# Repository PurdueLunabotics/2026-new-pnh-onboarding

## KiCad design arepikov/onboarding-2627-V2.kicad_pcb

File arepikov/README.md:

This is not your folder! Please make your own.

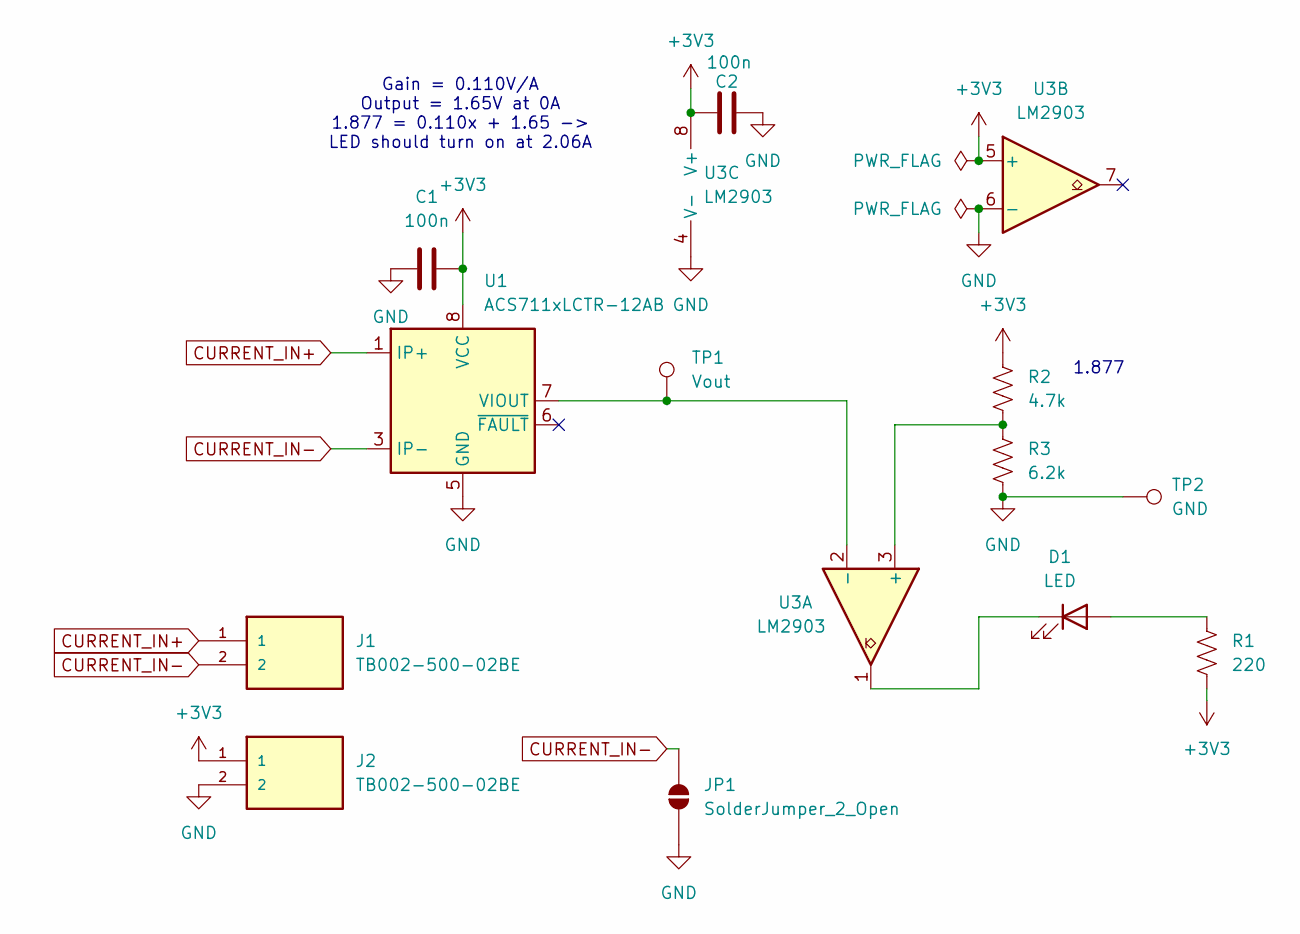
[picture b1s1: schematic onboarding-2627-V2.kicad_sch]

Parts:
C1, C2: 100n; C_0805_2012Metric
D1: LED; LED_D5.0mm
J1, J2: TB002-500-02BE; CUI_TB002-500-02BE
JP1: SolderJumper_2_Open; Wide_solderjumper
R1: 220; R_Axial_DIN0411_L9.9mm_D3.6mm_P12.70mm_Horizontal
R2: 4.7k; R_Axial_DIN0411_L9.9mm_D3.6mm_P12.70mm_Horizontal
R3: 6.2k; R_Axial_DIN0411_L9.9mm_D3.6mm_P12.70mm_Horizontal
TP1: Vout; TestPoint_Pad_D1.5mm
TP2: GND; TestPoint_Pad_D1.5mm
U1: ACS711xLCTR-12AB; SOIC-8_3.9x4.9mm_P1.27mm
U3: LM2903; DIP-8_W7.62mm

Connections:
+3V3: C1.2, C2.2, J2.1, R1.2, R2.1, U1.8 (VCC), U3.5 (+), U3.8 (V+)
CURRENT_IN+: J1.1, U1.1 (IP+), U1.2 (IP+)
CURRENT_IN-: J1.2, JP1.2 (B), U1.3 (IP-), U1.4 (IP-)
GND: C1.1, C2.1, J2.2, JP1.1 (A), R3.2, TP2.1 (1_1), U1.5 (GND), U3.4 (V-), U3.6 (-)
unnamed: D1.2 (A), R1.1
unnamed: D1.1 (K), U3.1
unnamed: TP1.1 (1_1), U1.7 (VIOUT), U3.2 (-)
unnamed: R2.2, R3.1, U3.3 (+)

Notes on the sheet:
Gain = 0.110V/A Output = 1.65V at 0A 1.877 = 0.110x + 1.65 -> LED should turn on at 2.06A
1.877

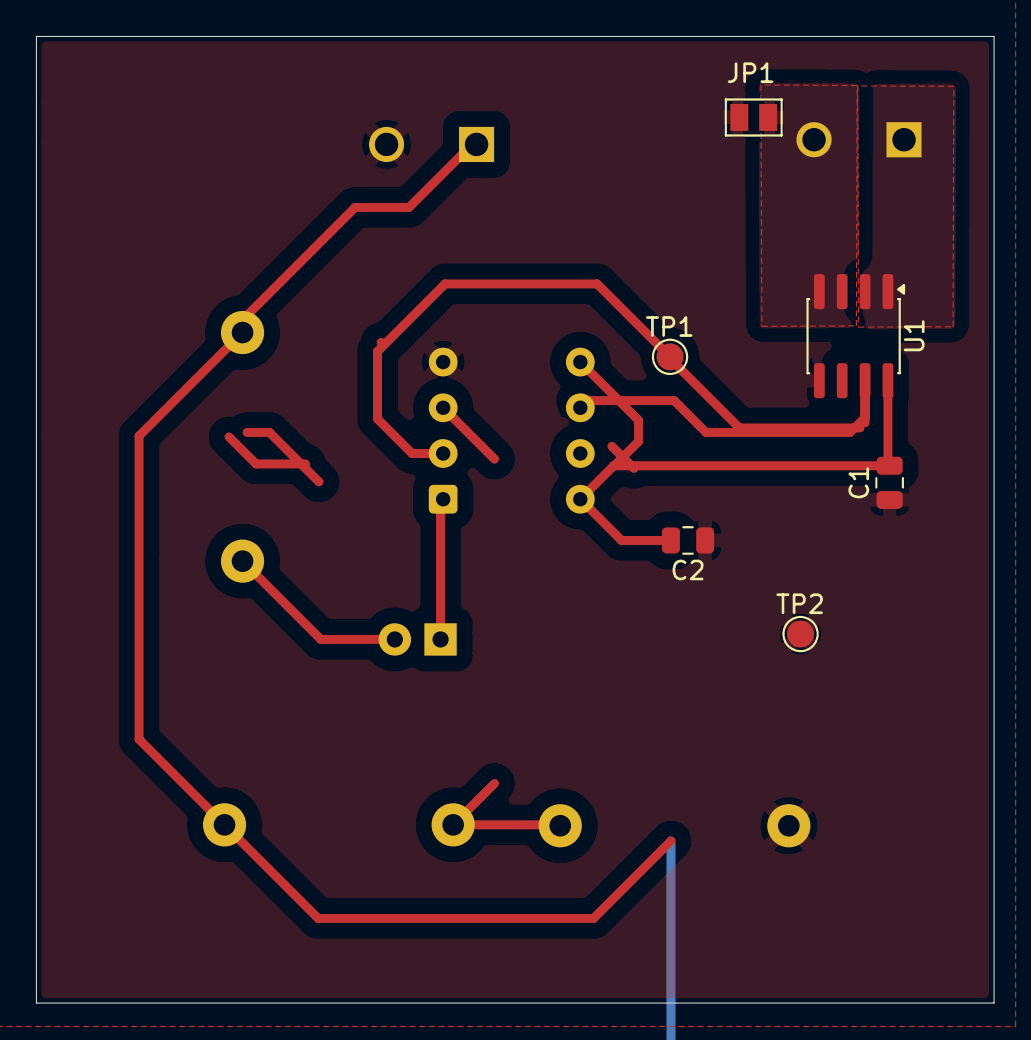
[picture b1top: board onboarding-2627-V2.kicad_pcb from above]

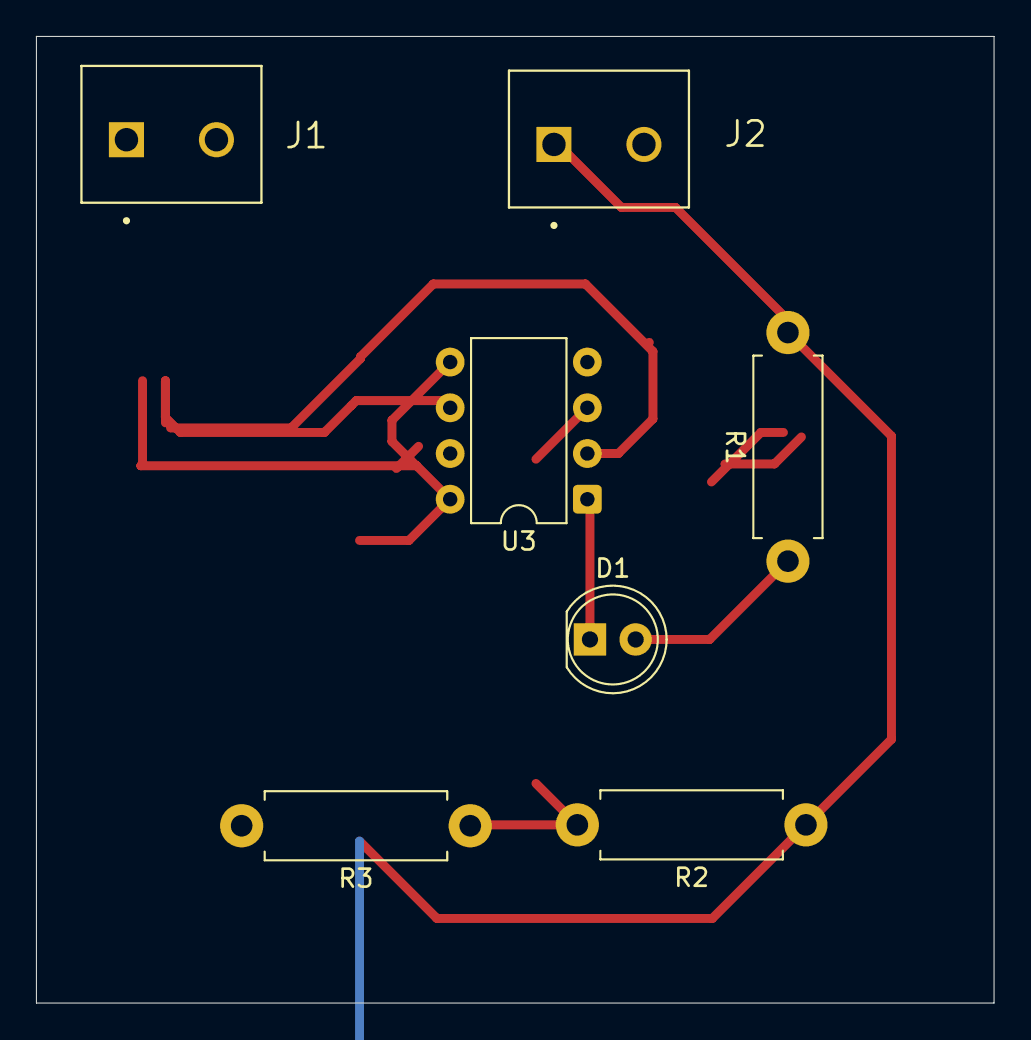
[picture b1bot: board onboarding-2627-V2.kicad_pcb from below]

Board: 2 copper layers, 53.2 x 53.7 mm, 13 parts (7 on the bottom side), 8 nets.

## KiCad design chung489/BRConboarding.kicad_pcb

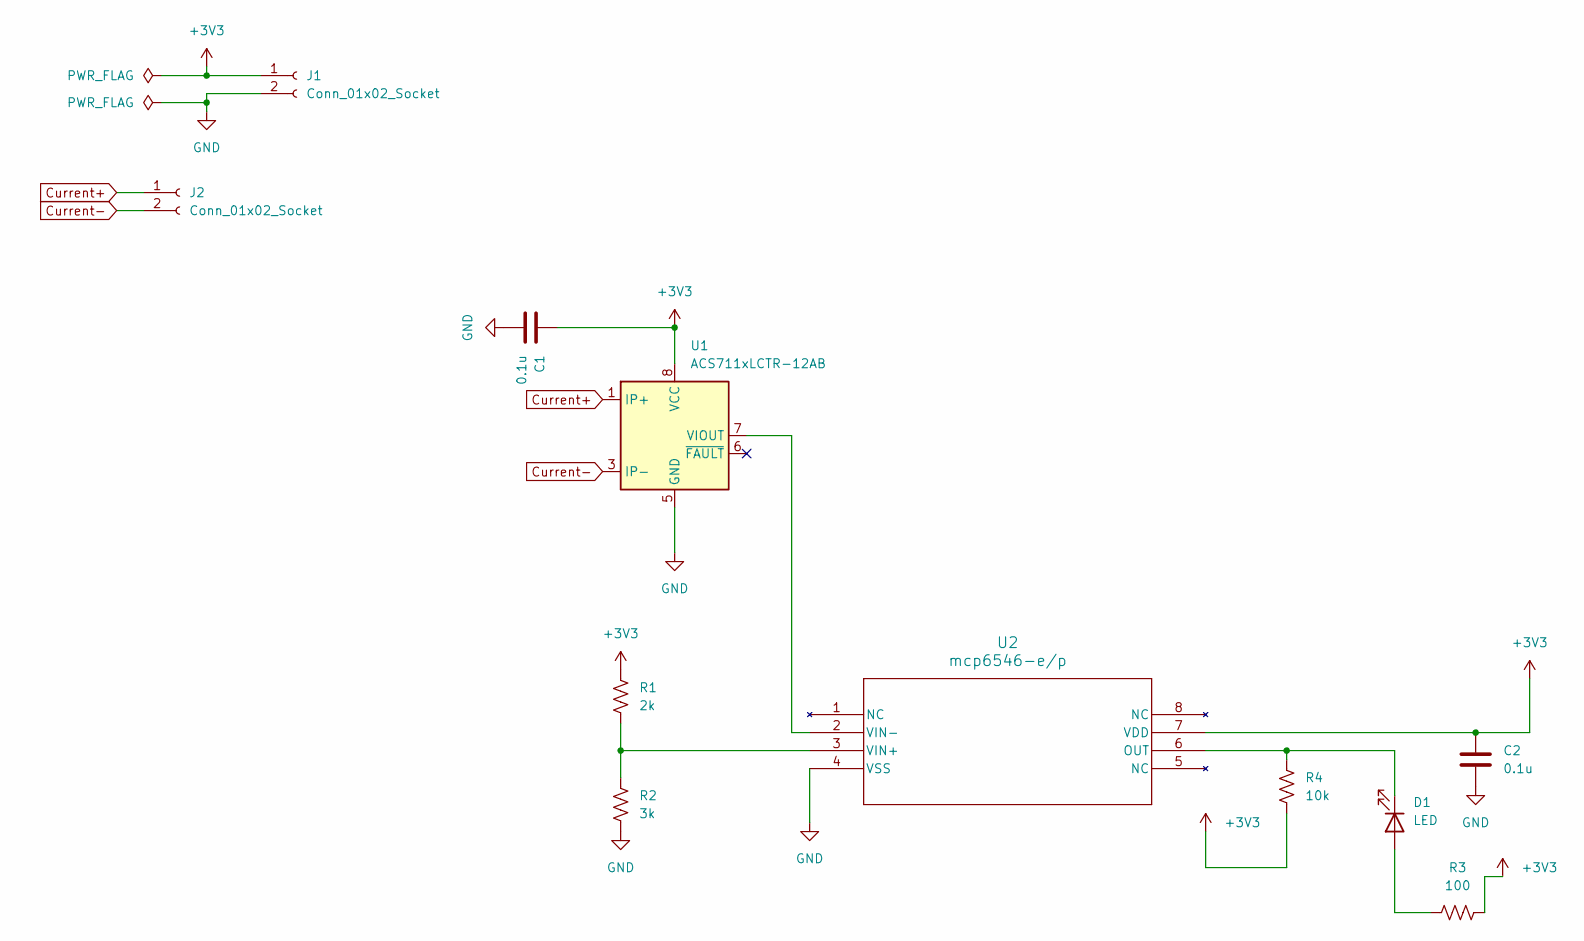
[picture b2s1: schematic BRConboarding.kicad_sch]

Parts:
C1, C2: 0.1u; C_0805_2012Metric
D1: LED; LED_D5.0mm
J1, J2: Conn_01x02_Socket; CUI_TB002-500-02BE
R1: 2k; R_Axial_DIN0411_L9.9mm_D3.6mm_P12.70mm_Horizontal
R2: 3k; R_Axial_DIN0411_L9.9mm_D3.6mm_P12.70mm_Horizontal
R3: 100; R_Axial_DIN0411_L9.9mm_D3.6mm_P12.70mm_Horizontal
R4: 10k; R_Axial_DIN0411_L9.9mm_D3.6mm_P12.70mm_Horizontal
U1: ACS711xLCTR-12AB; SOIC-8_3.9x4.9mm_P1.27mm
U2: mcp6546-e/p; DIP-8_W7.62mm

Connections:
+3V3: C1.1, C2.1, J1.1, R1.1, R3.2, R4.2, U1.8 (VCC), U2.7 (VDD)
Current+: J2.1, U1.1 (IP+), U1.2 (IP+)
Current-: J2.2, U1.3 (IP-), U1.4 (IP-)
GND: C1.2, C2.2, J1.2, R2.2, U1.5 (GND), U2.4 (VSS)
unnamed: D1.2 (A), R3.1
unnamed: D1.1 (K), R4.1, U2.6 (OUT)
unnamed: U1.7 (VIOUT), U2.2 (VIN-)
unnamed: R1.2, R2.1, U2.3 (VIN+)

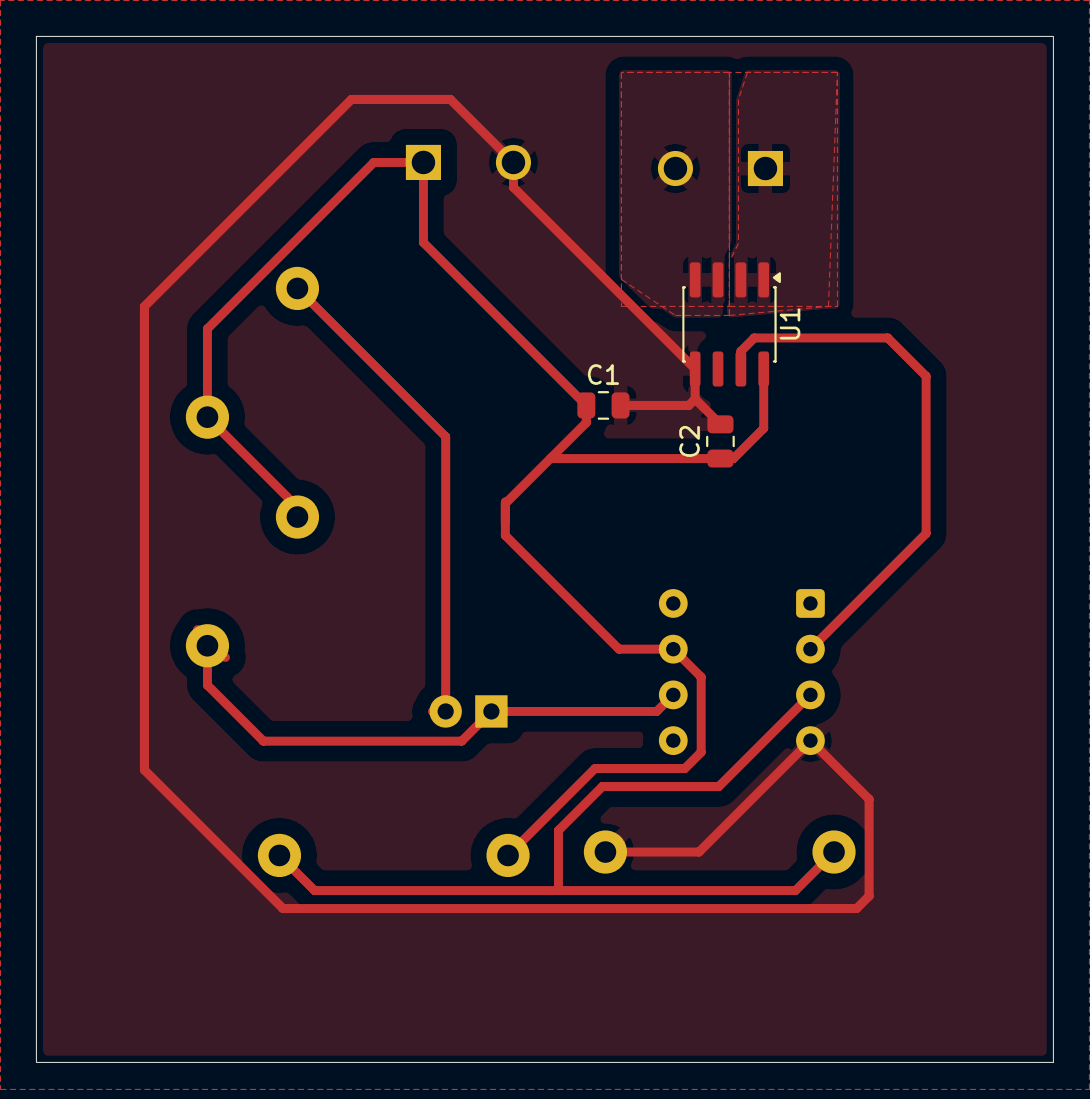
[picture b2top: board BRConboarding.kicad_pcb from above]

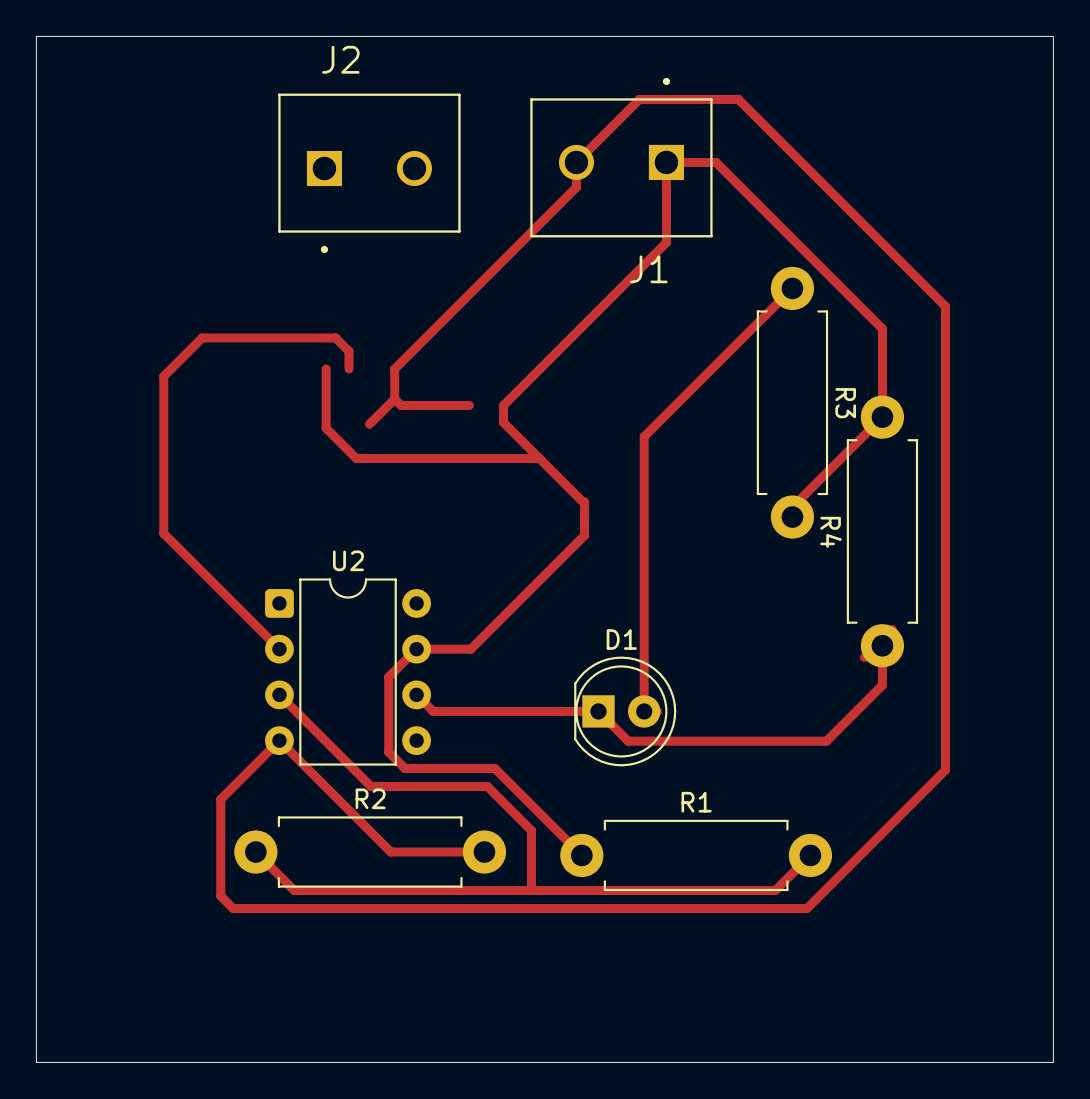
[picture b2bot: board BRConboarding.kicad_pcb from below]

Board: 2 copper layers, 56.5 x 57.0 mm, 11 parts (8 on the bottom side), 8 nets.
